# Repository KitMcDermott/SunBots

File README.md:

# SunBots
Sunbot Design Files 
Full tutorial is here: https://urbanarmor.org/instructions-for-smarter-plant-bots-v2/

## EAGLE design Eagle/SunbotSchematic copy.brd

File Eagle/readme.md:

these files are version 2 of the sunbot and uses an H Bridge, photocells, IR sensors/receivers and ultrasonic sensor. Version 3 uses xBee for communication.

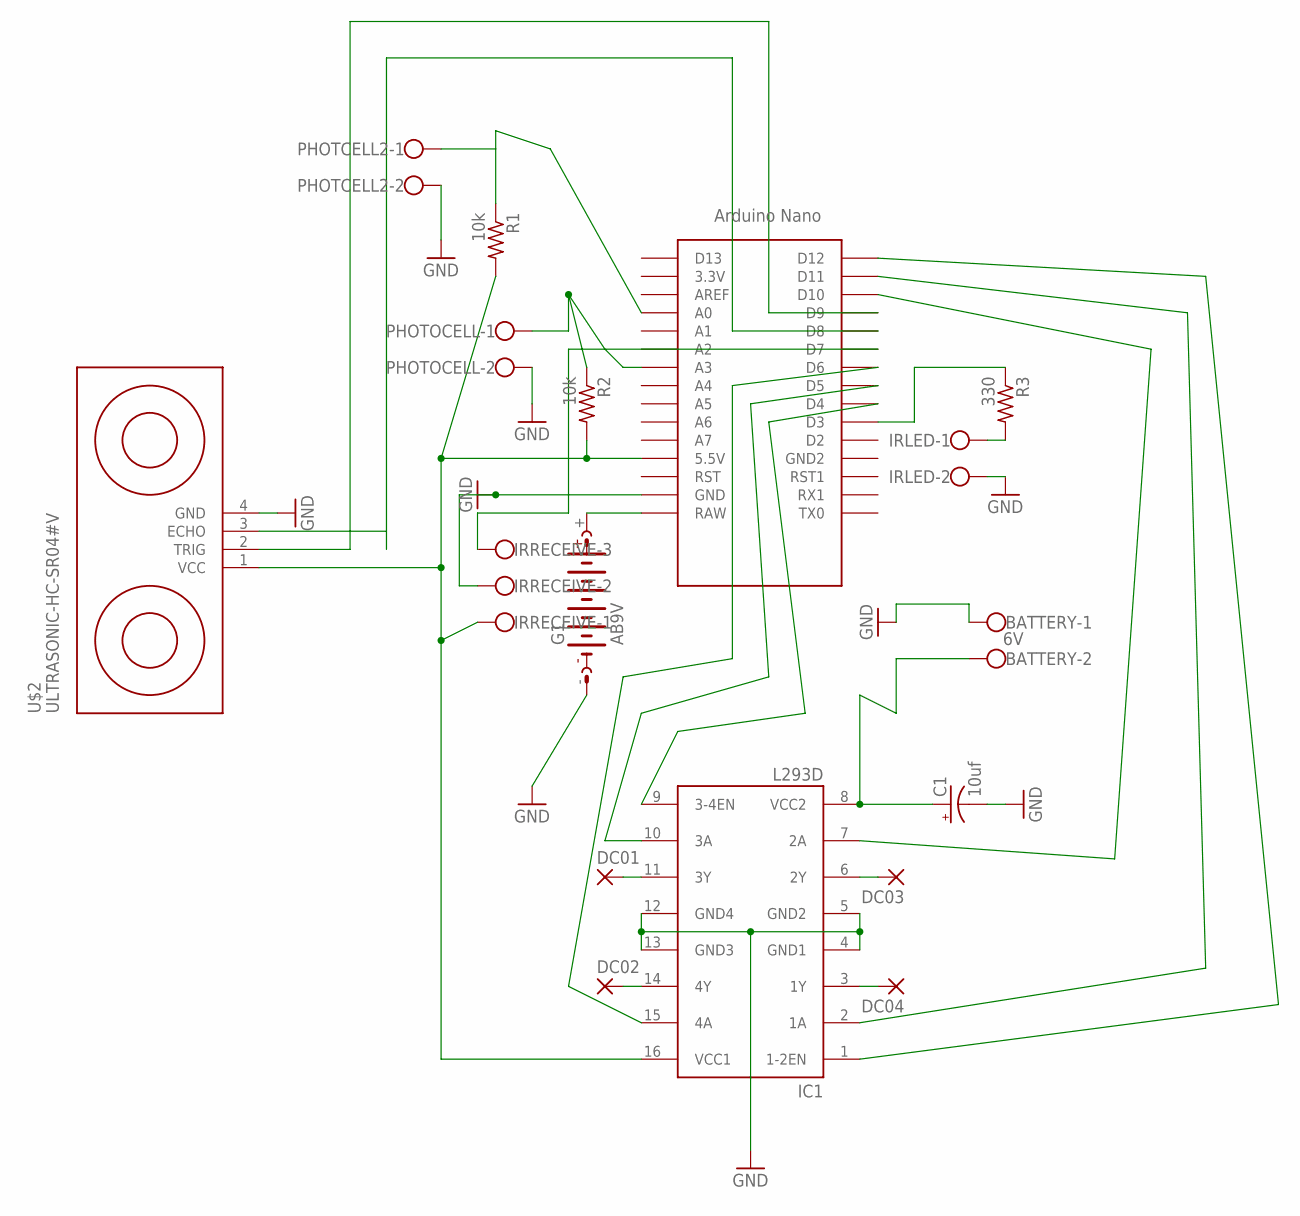
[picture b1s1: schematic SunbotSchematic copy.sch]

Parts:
BATTERY: 6V; W237-102
C1: 10uf; E2-5
DC01, DC02, DC03, DC04: WIREPAD1,6/0,8; 1,6/0,8
G1: AB9V
IC1: L293D; DIL16
IRLED: W237-102
IRRECEIVE: W237-103
PHOTCELL2: W237-102
PHOTOCELL: W237-102
R1, R2: 10k; 0204/7
R3: 330; 0204/7
U$1: NANO
U$2: ULTRASONIC-HC-SR04#V

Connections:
GND: BATTERY.1, C1.-, G1.-, IC1.4 (GND1), IC1.5 (GND2), IC1.12 (GND4), IC1.13 (GND3), IRLED.2, IRRECEIVE.2, PHOTCELL2.2, PHOTOCELL.2, U$1.GND, U$2.4 (GND)
unnamed: G1.+, U$1.RAW
unnamed: IC1.9 (3-4EN), U$1.D4
unnamed: IC1.10 (3A), U$1.D5
unnamed: IC1.15 (4A), U$1.D6
unnamed: DC01.1, IC1.11 (3Y)
unnamed: DC02.1, IC1.14 (4Y)
unnamed: DC03.1, IC1.6 (2Y)
unnamed: DC04.1, IC1.3 (1Y)
unnamed: IC1.1 (1-2EN), U$1.D12
unnamed: IC1.2 (1A), U$1.D11
unnamed: IC1.7 (2A), U$1.D10
unnamed: BATTERY.2, C1.+, IC1.8 (VCC2)
unnamed: U$1.D9, U$2.2 (TRIG)
unnamed: U$1.D8, U$2.3 (ECHO)
unnamed: PHOTOCELL.1, R2.1, U$1.A3
unnamed: PHOTCELL2.1, R1.1, U$1.A0
unnamed: IRLED.1, R3.2
unnamed: R3.1, U$1.D3
unnamed: IRRECEIVE.3, U$1.D7
PHOTOCELL: IC1.16 (VCC1), IRRECEIVE.1, R1.2, R2.2, U$1.5V (5.5V), U$2.1 (VCC)

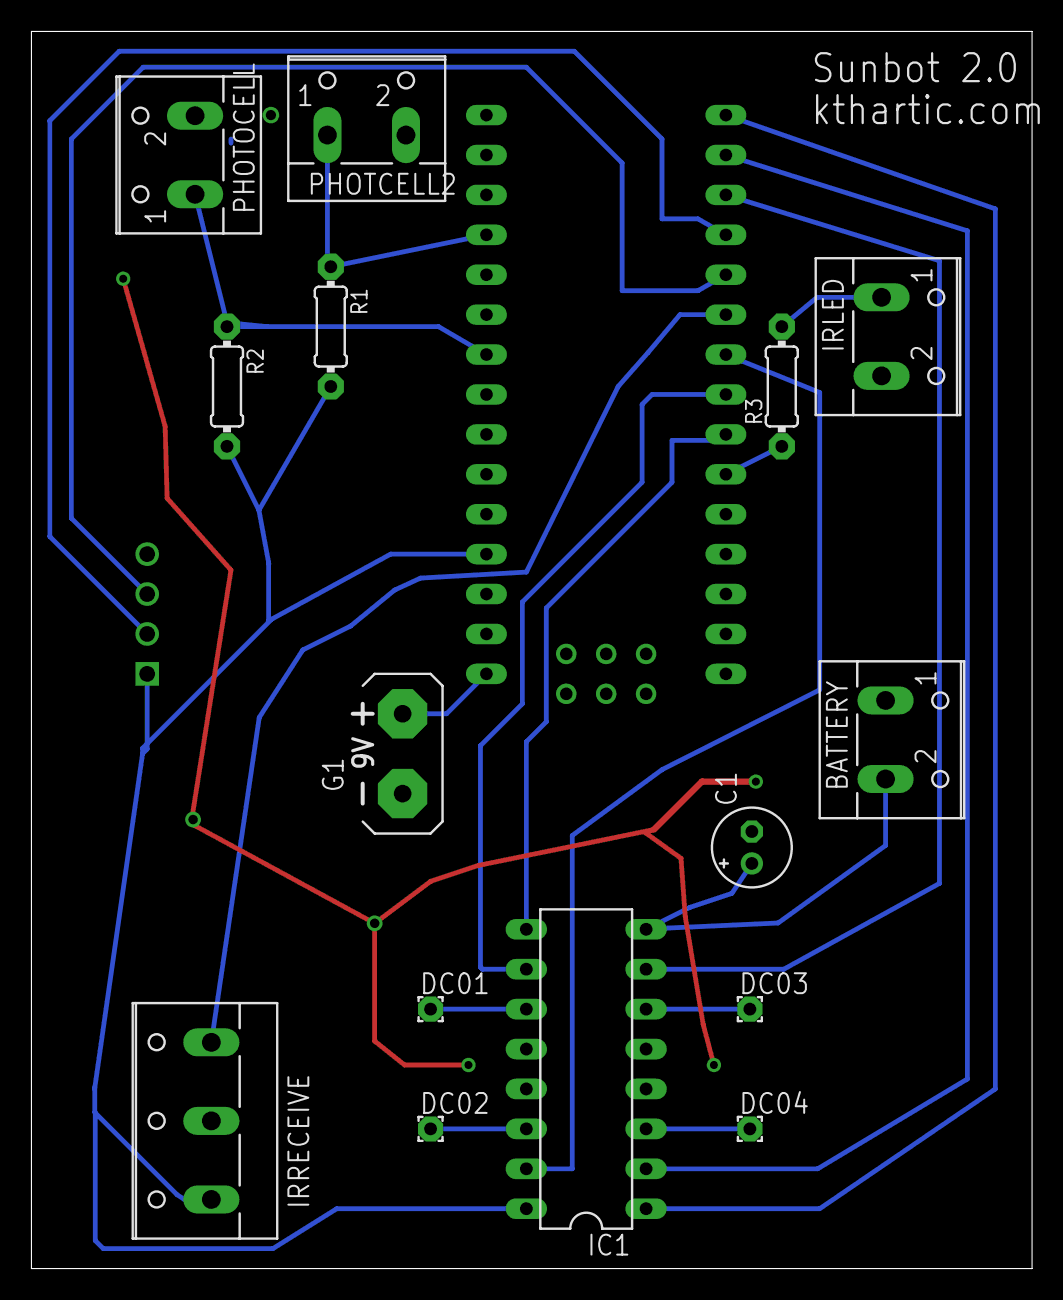
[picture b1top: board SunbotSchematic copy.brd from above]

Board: 2 copper layers, 63.7 x 78.7 mm, 17 parts (1 on the bottom side), 21 nets.

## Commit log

2024-04-02 Create readme.md
    Eagle Files ReadMe
2024-04-02 Add lasercut files
    files for laser cutting chassis and body.

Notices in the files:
parts and their libraries:
diy-modules: Released under the Creative Commons Attribution 4.0 International License: http://creativecommons.org/licenses/by/4.0
